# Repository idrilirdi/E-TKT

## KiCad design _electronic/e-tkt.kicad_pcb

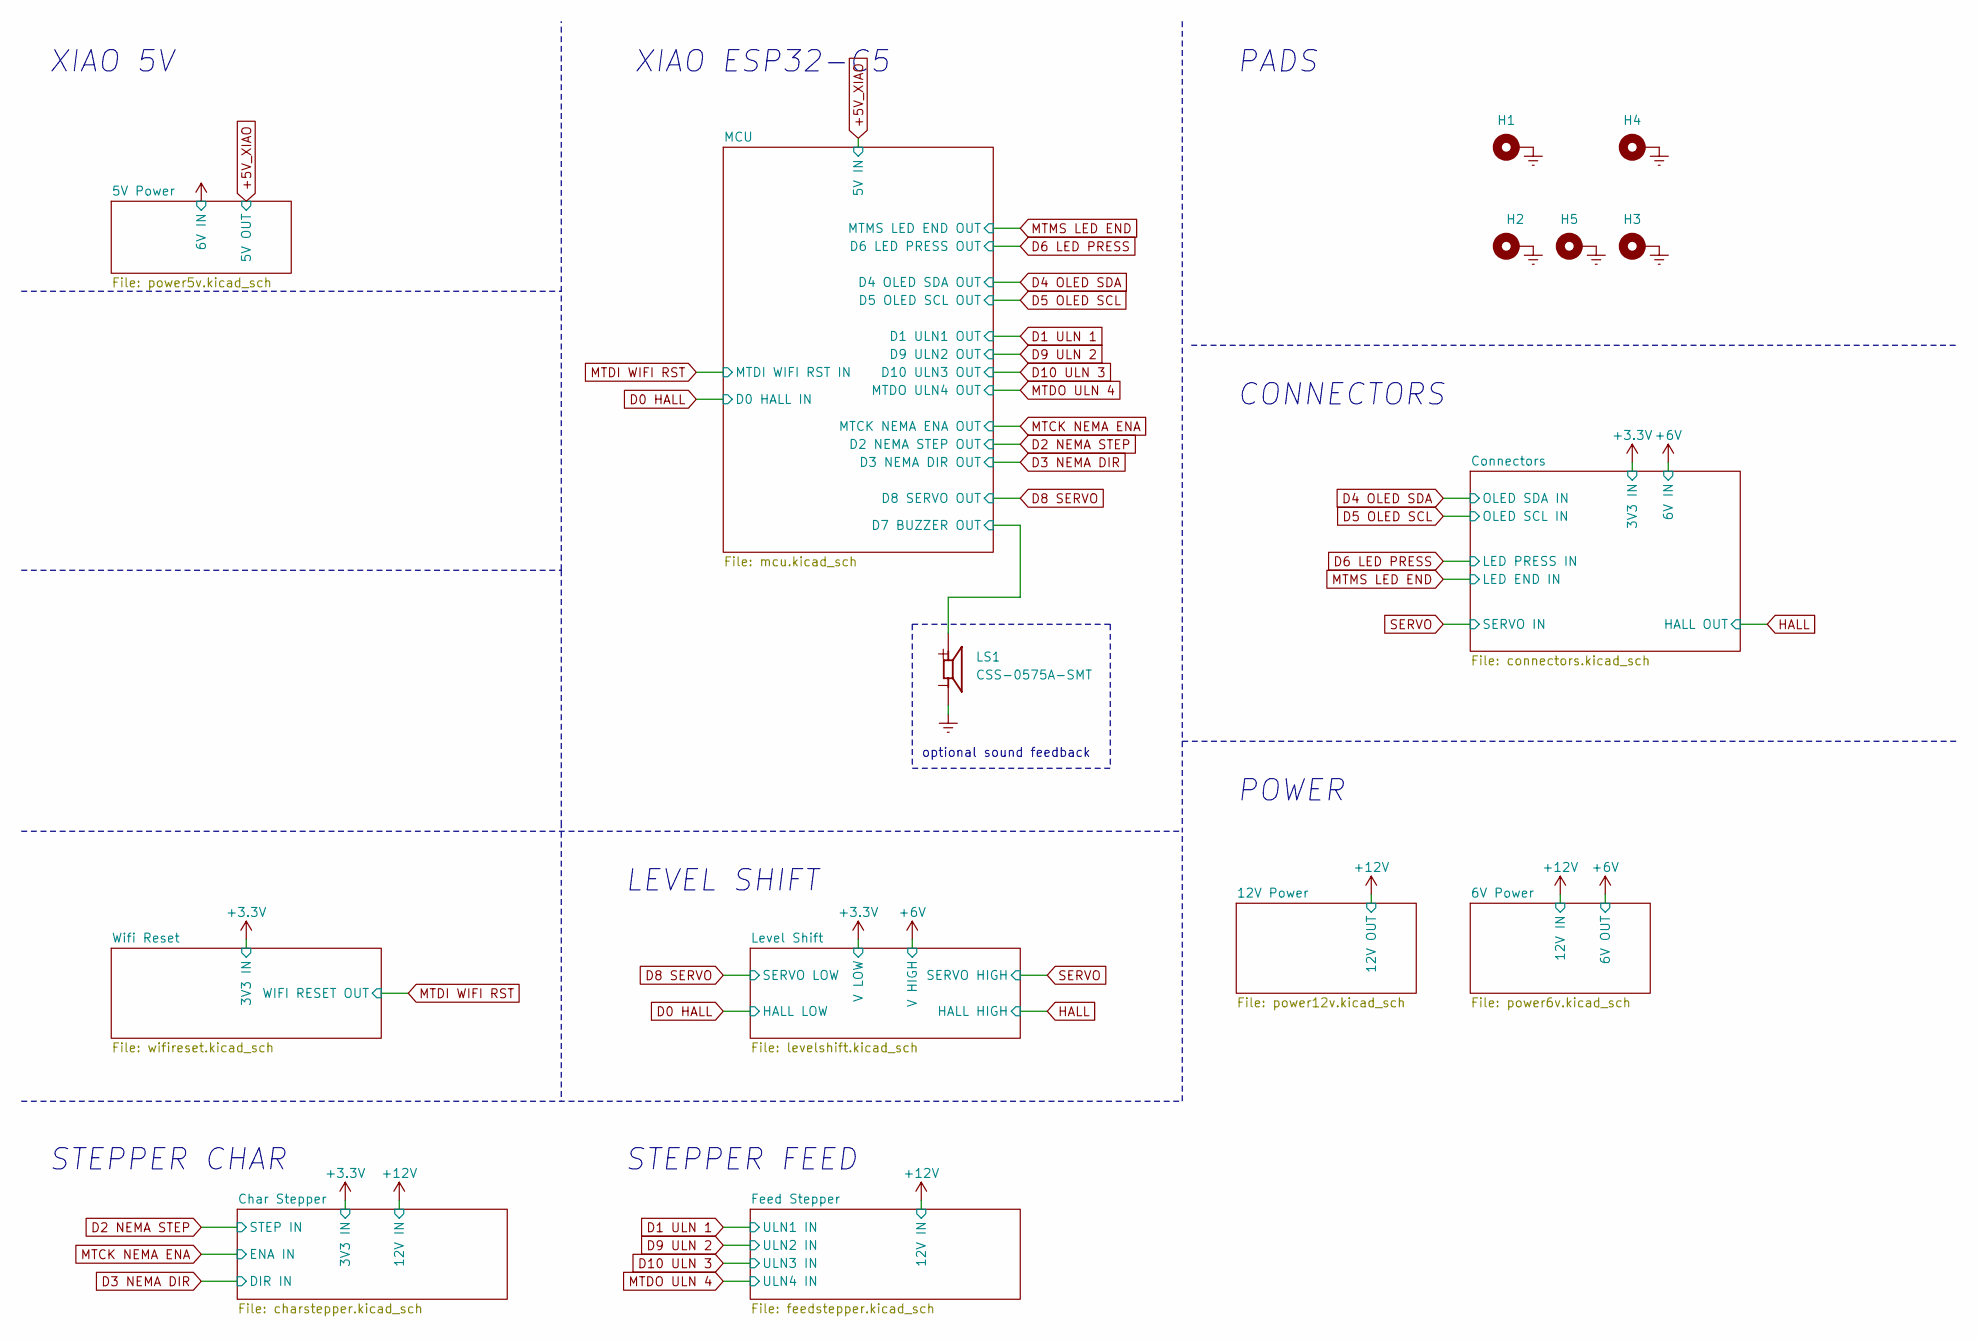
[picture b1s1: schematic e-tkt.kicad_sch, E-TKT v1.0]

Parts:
H1, H2, H3, H4, H5: M3; MountingHole_3.2mm_M3_Pad_Via; Mouser OK
LS1: CSS-0575A-SMT; CUI_CSS-0575A-SMT; Mouser OK

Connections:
/MCU/D7 BUZZER OUT: LS1.1; also elsewhere on the board
GNDREF: H1.1, H2.1, H3.1, H4.1, H5.1, LS1.2; also elsewhere on the board

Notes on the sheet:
PADS
POWER
optional sound feedback
CONNECTORS
STEPPER CHAR
XIAO ESP32-C5
LEVEL SHIFT
STEPPER FEED
XIAO 5V

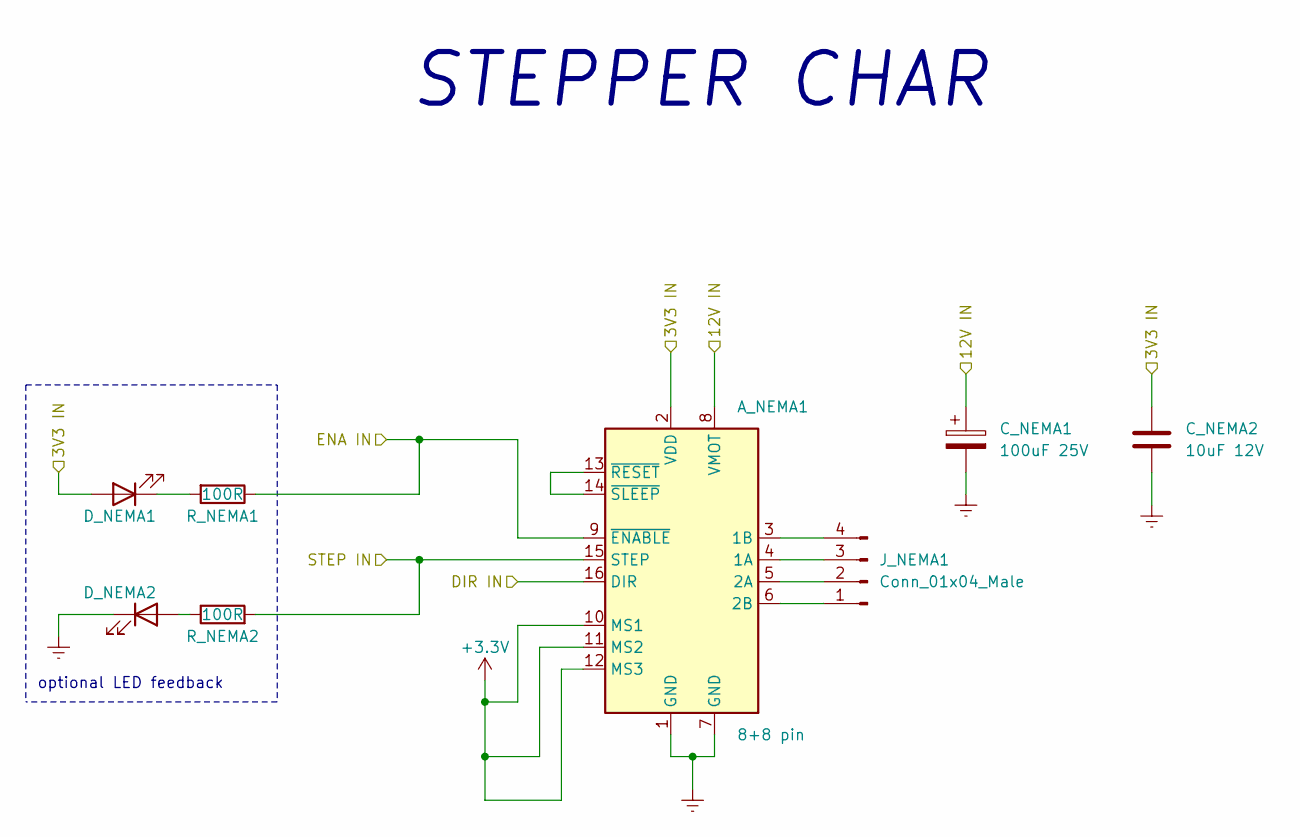
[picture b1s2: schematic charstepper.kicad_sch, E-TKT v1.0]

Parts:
A_NEMA1: 8+8 pin; Pololu_Breakout-16_15.2x20.3mm; Mouser OK
C_NEMA1: 100uF 25V; CP_Elec_6.3x7.7; Mouser OK
C_NEMA2: 10uF 12V; C_0603_1608Metric_Pad1.08x0.95mm_HandSolder; Mouser OK
D_NEMA1, D_NEMA2: LED white; LED_0603_1608Metric_Pad1.05x0.95mm_HandSolder; Mouser OK
J_NEMA1: Conn_01x04_Male; PinHeader_1x04_P2.54mm_Horizontal; Mouser OK
R_NEMA1, R_NEMA2: 100R; R_0603_1608Metric_Pad0.98x0.95mm_HandSolder; Mouser OK

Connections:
+3.3V: A_NEMA1.2 (VDD), A_NEMA1.10 (MS1), A_NEMA1.11 (MS2), A_NEMA1.12 (MS3), C_NEMA2.2, D_NEMA1.2 (A); also elsewhere on the board
+12V: A_NEMA1.8 (VMOT), C_NEMA1.1; also elsewhere on the board
D2 NEMA STEP: A_NEMA1.15 (STEP), R_NEMA2.2; also elsewhere on the board
D3 NEMA DIR: A_NEMA1.16 (DIR); also elsewhere on the board
GNDREF: A_NEMA1.1 (GND), A_NEMA1.7 (GND), C_NEMA1.2, C_NEMA2.1, D_NEMA2.1 (K); also elsewhere on the board
MTCK NEMA ENA: A_NEMA1.9 (~ENABLE), R_NEMA1.1; also elsewhere on the board
unnamed: A_NEMA1.4 (1A), J_NEMA1.3
unnamed: A_NEMA1.3 (1B), J_NEMA1.4
unnamed: A_NEMA1.5 (2A), J_NEMA1.2
unnamed: A_NEMA1.6 (2B), J_NEMA1.1
unnamed: A_NEMA1.13 (~RESET), A_NEMA1.14 (~SLEEP)
unnamed: D_NEMA1.1 (K), R_NEMA1.2
unnamed: D_NEMA2.2 (A), R_NEMA2.1

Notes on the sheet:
optional LED feedback
STEPPER CHAR

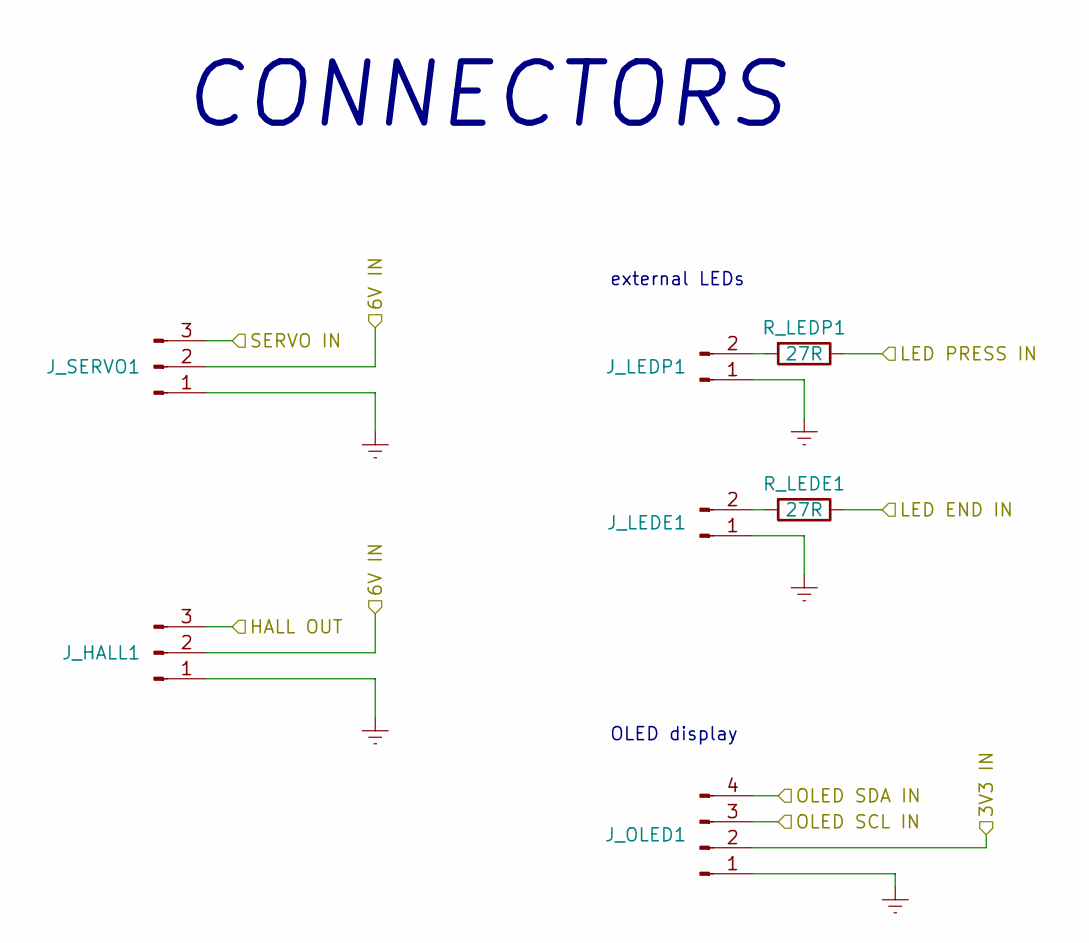
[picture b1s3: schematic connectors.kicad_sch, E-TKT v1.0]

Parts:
J_HALL1: Conn_01x03_Female; PinHeader_1x03_P2.54mm_Vertical; Mouser OK
J_LEDE1: Conn_01x02_Male; PinHeader_1x02_P2.54mm_Vertical; Mouser OK
J_LEDP1: Conn_01x02_Male; PinHeader_1x02_P2.54mm_Vertical; Mouser OK
J_OLED1: Conn_01x04_Male; PinHeader_1x04_P2.54mm_Vertical; Mouser OK
J_SERVO1: Conn_01x03_Male; PinHeader_1x03_P2.54mm_Vertical; Mouser OK
R_LEDE1: 27R; R_0603_1608Metric_Pad0.98x0.95mm_HandSolder; Mouser OK
R_LEDP1: 27R; R_0603_1608Metric_Pad0.98x0.95mm_HandSolder; Mouser OK

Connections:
+3.3V: J_OLED1.2; also elsewhere on the board
+6V: J_HALL1.2, J_SERVO1.2; also elsewhere on the board
D4 OLED SDA: J_OLED1.4; also elsewhere on the board
D5 OLED SCL: J_OLED1.3; also elsewhere on the board
D6 LED PRESS: R_LEDP1.1; also elsewhere on the board
GNDREF: J_HALL1.1, J_LEDE1.1, J_LEDP1.1, J_OLED1.1, J_SERVO1.1; also elsewhere on the board
HALL: J_HALL1.3; also elsewhere on the board
MTMS LED END: R_LEDE1.1; also elsewhere on the board
unnamed: J_LEDE1.2, R_LEDE1.2
unnamed: J_LEDP1.2, R_LEDP1.2
SERVO: J_SERVO1.3; also elsewhere on the board

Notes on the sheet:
OLED display
CONNECTORS
external LEDs

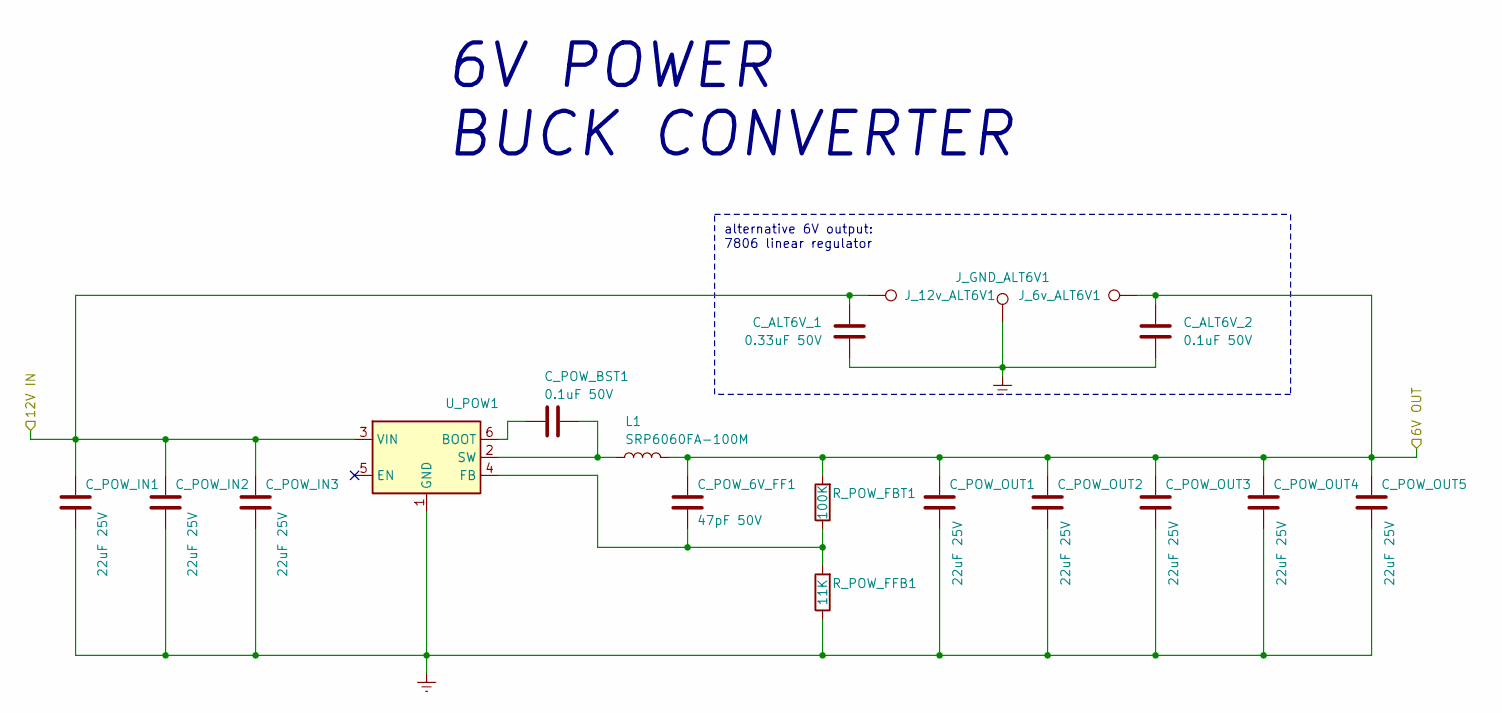
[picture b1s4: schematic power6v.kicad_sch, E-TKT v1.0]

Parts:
C_ALT6V_1: 0.33uF 50V; C_0603_1608Metric_Pad1.08x0.95mm_HandSolder; Mouser OK
C_ALT6V_2: 0.1uF 50V; C_0603_1608Metric_Pad1.08x0.95mm_HandSolder; Mouser OK
C_POW_6V_FF1: 47pF 50V; C_0603_1608Metric_Pad1.08x0.95mm_HandSolder; Mouser OK
C_POW_BST1: 0.1uF 50V; C_0603_1608Metric_Pad1.08x0.95mm_HandSolder; Mouser OK
C_POW_IN1, C_POW_IN2, C_POW_IN3: 22uF 25V; C_1210_3225Metric_Pad1.33x2.70mm_HandSolder; Mouser OK
C_POW_OUT1, C_POW_OUT2, C_POW_OUT3, C_POW_OUT4, C_POW_OUT5: 22uF 25V; C_1210_3225Metric_Pad1.33x2.70mm_HandSolder; Mouser OK
J_6v_ALT6V1, J_12v_ALT6V1: TestPoint; TestPoint_Pad_D1.5mm; Mouser OK
J_GND_ALT6V1: TestPoint; TestPoint_Pad_D1.5mm; Mouser OK
L1: SRP6060FA-100M; SRP6060FA-4R7M; Mouser OK
R_POW_FBT1: 100K; R_0603_1608Metric_Pad0.98x0.95mm_HandSolder; Mouser OK
R_POW_FFB1: 11K; R_0603_1608Metric_Pad0.98x0.95mm_HandSolder; Mouser OK
U_POW1: SOT-23-6_Handsoldering; Mouser N

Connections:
+6V: C_ALT6V_2.1, C_POW_6V_FF1.1, C_POW_OUT1.1, C_POW_OUT2.1, C_POW_OUT3.1, C_POW_OUT4.1, C_POW_OUT5.1, J_6v_ALT6V1.1, L1.2, R_POW_FBT1.2; also elsewhere on the board
+12V: C_ALT6V_1.2, C_POW_IN1.1, C_POW_IN2.1, C_POW_IN3.1, J_12v_ALT6V1.1, U_POW1.3 (VIN); also elsewhere on the board
GNDREF: C_ALT6V_1.1, C_ALT6V_2.2, C_POW_IN1.2, C_POW_IN2.2, C_POW_IN3.2, C_POW_OUT1.2, C_POW_OUT2.2, C_POW_OUT3.2, C_POW_OUT4.2, C_POW_OUT5.2, J_GND_ALT6V1.1, R_POW_FFB1.1, U_POW1.1 (GND); also elsewhere on the board
unnamed: C_POW_BST1.1, U_POW1.6 (BOOT)
unnamed: C_POW_6V_FF1.2, R_POW_FBT1.1, R_POW_FFB1.2, U_POW1.4 (FB)
unnamed: C_POW_BST1.2, L1.1, U_POW1.2 (SW)

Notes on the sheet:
alternative 6V output: 7806 linear regulator
6V POWER BUCK CONVERTER

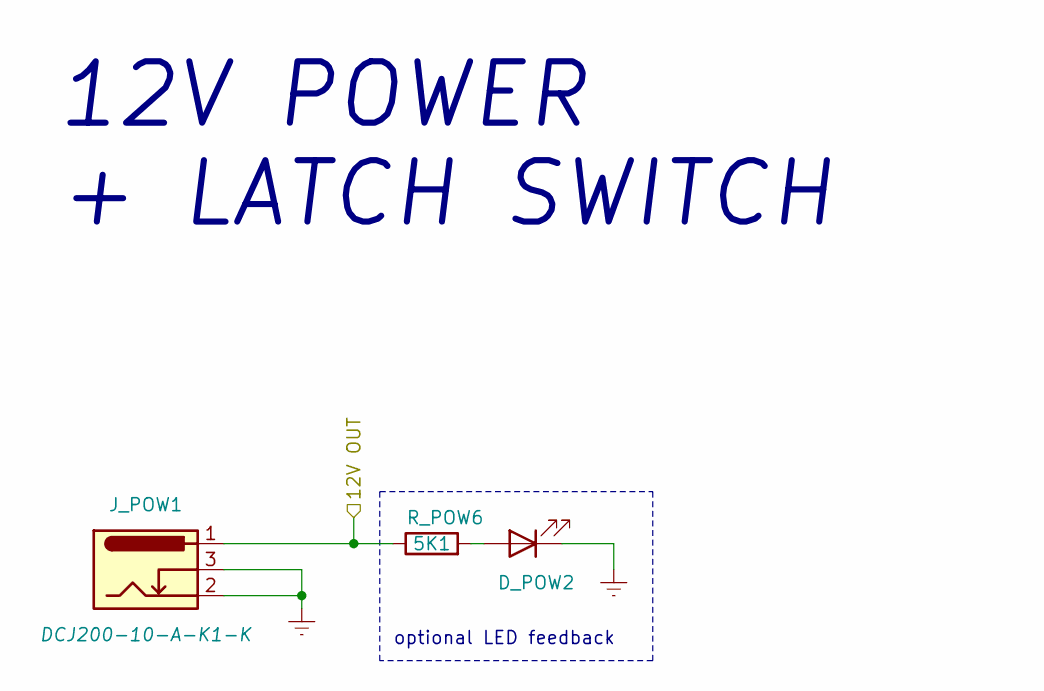
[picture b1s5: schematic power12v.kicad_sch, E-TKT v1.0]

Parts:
D_POW2: LED white; LED_0603_1608Metric_Pad1.05x0.95mm_HandSolder; Mouser OK
J_POW1: Barrel_Jack_Switch; BarrelJack_GCT_DCJ200-10-A_Horizontal; Mouser OK
R_POW6: 5K1; R_0603_1608Metric_Pad0.98x0.95mm_HandSolder; Mouser OK

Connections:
+12V: J_POW1.1, R_POW6.1; also elsewhere on the board
GNDREF: D_POW2.1 (K), J_POW1.2, J_POW1.3; also elsewhere on the board
unnamed: D_POW2.2 (A), R_POW6.2

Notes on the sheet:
optional LED feedback
12V POWER + LATCH SWITCH

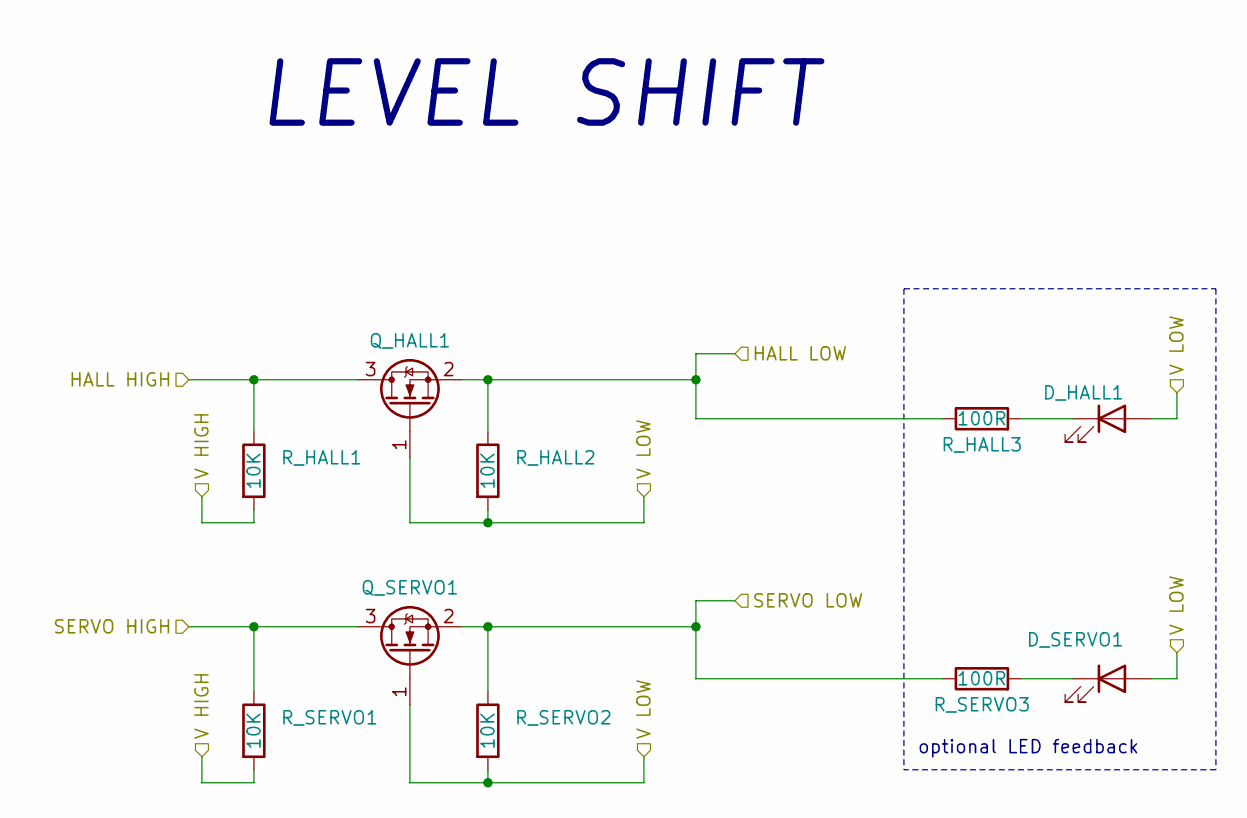
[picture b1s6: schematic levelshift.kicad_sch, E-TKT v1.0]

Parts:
D_HALL1: LED white; LED_0603_1608Metric_Pad1.05x0.95mm_HandSolder; Mouser OK
D_SERVO1: LED white; LED_0603_1608Metric_Pad1.05x0.95mm_HandSolder; Mouser OK
Q_HALL1: BSS138LT3G; SOT-23_Handsoldering; Mouser OK
Q_SERVO1: BSS138LT3G; SOT-23_Handsoldering; Mouser OK
R_HALL1, R_HALL2: 10K; R_0603_1608Metric_Pad0.98x0.95mm_HandSolder; Mouser OK
R_HALL3: 100R; R_0603_1608Metric_Pad0.98x0.95mm_HandSolder; Mouser OK
R_SERVO1, R_SERVO2: 10K; R_0603_1608Metric_Pad0.98x0.95mm_HandSolder; Mouser OK
R_SERVO3: 100R; R_0603_1608Metric_Pad0.98x0.95mm_HandSolder; Mouser OK

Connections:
+3.3V: D_HALL1.2 (A), D_SERVO1.2 (A), Q_HALL1.1 (G), Q_SERVO1.1 (G), R_HALL2.2, R_SERVO2.2; also elsewhere on the board
+6V: R_HALL1.2, R_SERVO1.2; also elsewhere on the board
D0 HALL: Q_HALL1.2 (S), R_HALL2.1, R_HALL3.1; also elsewhere on the board
D8 SERVO: Q_SERVO1.2 (S), R_SERVO2.1, R_SERVO3.1; also elsewhere on the board
HALL: Q_HALL1.3 (D), R_HALL1.1; also elsewhere on the board
unnamed: D_HALL1.1 (K), R_HALL3.2
unnamed: D_SERVO1.1 (K), R_SERVO3.2
SERVO: Q_SERVO1.3 (D), R_SERVO1.1; also elsewhere on the board

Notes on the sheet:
optional LED feedback
LEVEL SHIFT

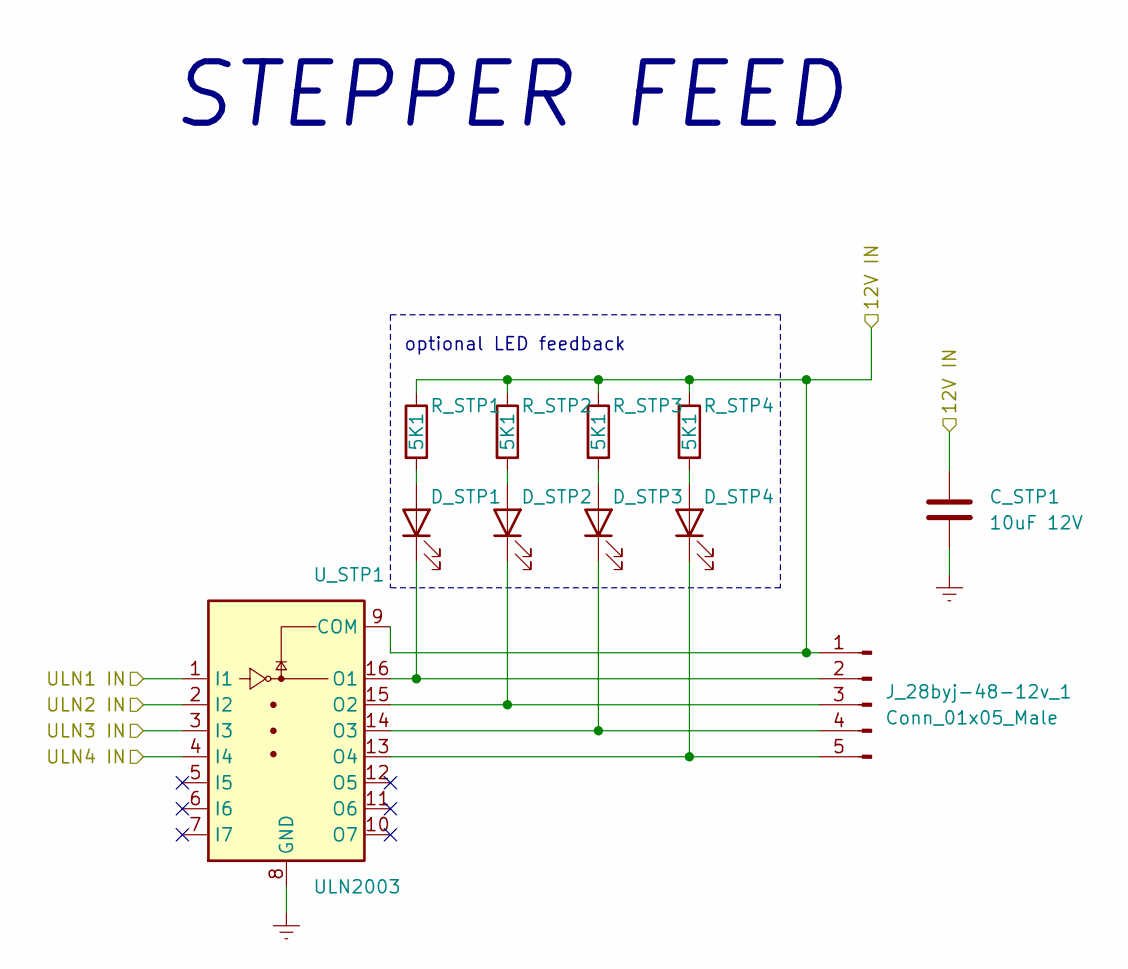
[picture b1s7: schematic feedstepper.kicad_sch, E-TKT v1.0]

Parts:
C_STP1: 10uF 12V; C_0603_1608Metric_Pad1.08x0.95mm_HandSolder; Mouser OK
D_STP1, D_STP2, D_STP3, D_STP4: LED white; LED_0603_1608Metric_Pad1.05x0.95mm_HandSolder; Mouser OK
J_28byj-48-12v_1: Conn_01x05_Male; PinHeader_1x05_P2.54mm_Vertical; Mouser OK
R_STP1, R_STP2, R_STP3, R_STP4: 5K1; R_0603_1608Metric_Pad0.98x0.95mm_HandSolder; Mouser OK
U_STP1: ULN2003; SOIC-16_3.9x9.9mm_P1.27mm; Mouser OK

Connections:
+12V: C_STP1.2, J_28byj-48-12v_1.1, R_STP1.1, R_STP2.1, R_STP3.1, R_STP4.1, U_STP1.9 (COM); also elsewhere on the board
D1 ULN 1: U_STP1.1 (I1); also elsewhere on the board
D9 ULN 2: U_STP1.2 (I2); also elsewhere on the board
D10 ULN 3: U_STP1.3 (I3); also elsewhere on the board
GNDREF: C_STP1.1, U_STP1.8 (GND); also elsewhere on the board
MTDO ULN 4: U_STP1.4 (I4); also elsewhere on the board
unnamed: D_STP1.2 (A), R_STP1.2
unnamed: D_STP1.1 (K), J_28byj-48-12v_1.2, U_STP1.16 (O1)
unnamed: D_STP2.2 (A), R_STP2.2
unnamed: D_STP2.1 (K), J_28byj-48-12v_1.3, U_STP1.15 (O2)
unnamed: D_STP3.2 (A), R_STP3.2
unnamed: D_STP3.1 (K), J_28byj-48-12v_1.4, U_STP1.14 (O3)
unnamed: D_STP4.2 (A), R_STP4.2
unnamed: D_STP4.1 (K), J_28byj-48-12v_1.5, U_STP1.13 (O4)

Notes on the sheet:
optional LED feedback
STEPPER FEED

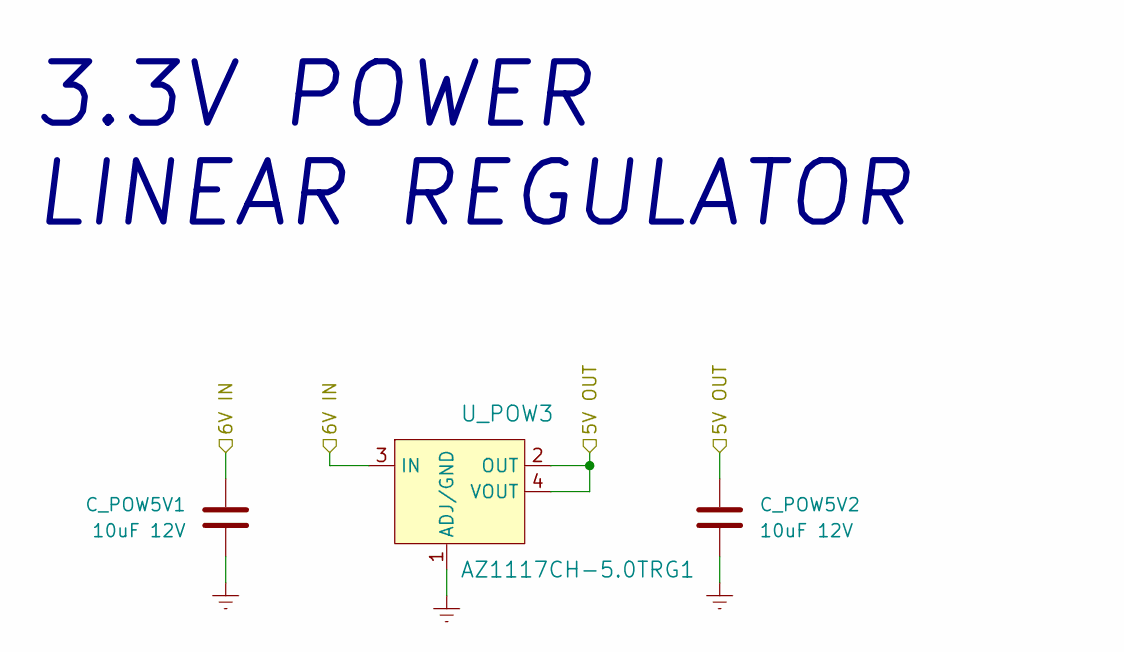
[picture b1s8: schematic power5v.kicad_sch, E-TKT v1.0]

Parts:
C_POW5V1, C_POW5V2: 10uF 12V; C_0603_1608Metric_Pad1.08x0.95mm_HandSolder; Mouser OK
U_POW3: AZ1117CH-5.0TRG1; SOT-223; Mouser OK

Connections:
+5V_XIAO: C_POW5V2.1, U_POW3.2 (OUT), U_POW3.4 (VOUT); also elsewhere on the board
+6V: C_POW5V1.1, U_POW3.3 (IN); also elsewhere on the board
GNDREF: C_POW5V1.2, C_POW5V2.2, U_POW3.1 (ADJ/GND); also elsewhere on the board

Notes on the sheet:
3.3V POWER LINEAR REGULATOR

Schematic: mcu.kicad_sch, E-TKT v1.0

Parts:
D_VBUS1: SS14; D_SMA
SW_DFU1: B3FS-1000
U_MCU1: XIAO-ESP32-C5; XIAO-ESP32-C5-SMD

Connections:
+3.3V: U_MCU1.12 (3V3_OUT); also elsewhere on the board
+5V_XIAO: D_VBUS1.2 (A); also elsewhere on the board
/MCU/D7 BUZZER OUT: U_MCU1.8 (D7); also elsewhere on the board
D0 HALL: U_MCU1.1 (D0); also elsewhere on the board
D1 ULN 1: U_MCU1.2 (D1); also elsewhere on the board
D2 NEMA STEP: U_MCU1.3 (D2); also elsewhere on the board
D3 NEMA DIR: U_MCU1.4 (D3); also elsewhere on the board
D4 OLED SDA: U_MCU1.5 (D4); also elsewhere on the board
D5 OLED SCL: U_MCU1.6 (D5); also elsewhere on the board
D6 LED PRESS: U_MCU1.7 (D6); also elsewhere on the board
D8 SERVO: U_MCU1.9 (D8); also elsewhere on the board
D9 ULN 2: U_MCU1.10 (D9); also elsewhere on the board
D10 ULN 3: U_MCU1.11 (D10); also elsewhere on the board
GNDREF: SW_DFU1.2, SW_DFU1.4, U_MCU1.13 (GND), U_MCU1.18 (GND), U_MCU1.24 (GND), U_MCU1.25 (PAD); also elsewhere on the board
MTCK NEMA ENA: U_MCU1.20 (MTCK); also elsewhere on the board
MTDI WIFI RST: U_MCU1.15 (MTDI); also elsewhere on the board
MTDO ULN 4: U_MCU1.16 (MTDO); also elsewhere on the board
MTMS LED END: U_MCU1.19 (MTMS); also elsewhere on the board
unnamed: D_VBUS1.1 (K), U_MCU1.14 (VBUS)
unnamed: SW_DFU1.1, SW_DFU1.3, U_MCU1.21 (BOOT)

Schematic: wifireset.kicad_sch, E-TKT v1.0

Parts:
C_WIFI1: 0.1uF 50V; C_0603_1608Metric_Pad1.08x0.95mm_HandSolder; Mouser OK
R_WIFI1: 10K; R_0603_1608Metric_Pad0.98x0.95mm_HandSolder; Mouser OK
SW_WIFI1: B3FS-1000; Mouser OK

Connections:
+3.3V: R_WIFI1.2; also elsewhere on the board
GNDREF: C_WIFI1.1, SW_WIFI1.1, SW_WIFI1.2; also elsewhere on the board
MTDI WIFI RST: C_WIFI1.2, R_WIFI1.1, SW_WIFI1.3, SW_WIFI1.4; also elsewhere on the board

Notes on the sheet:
WIFI RESET

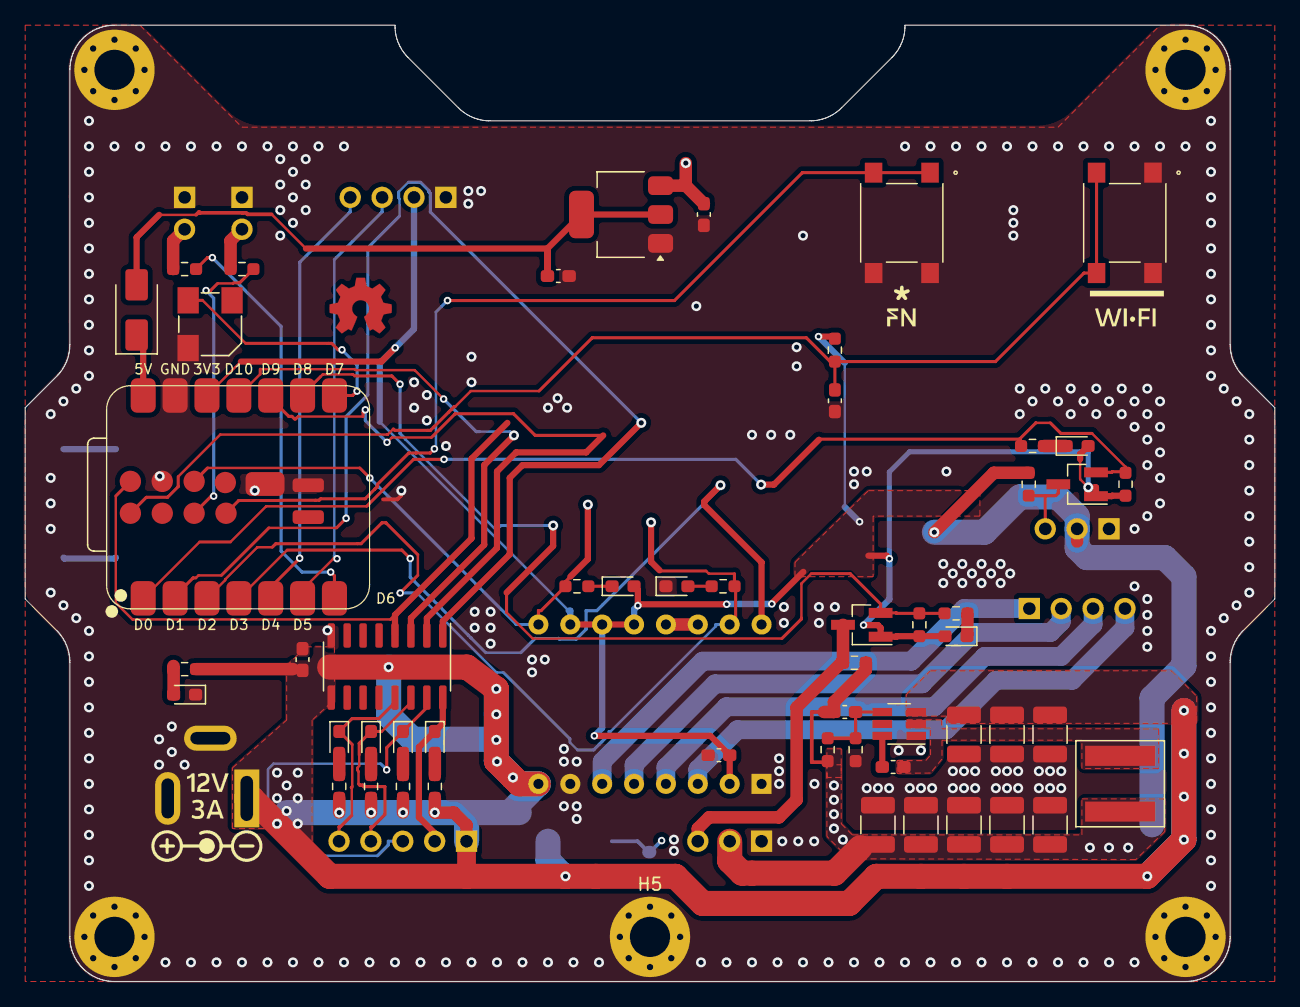
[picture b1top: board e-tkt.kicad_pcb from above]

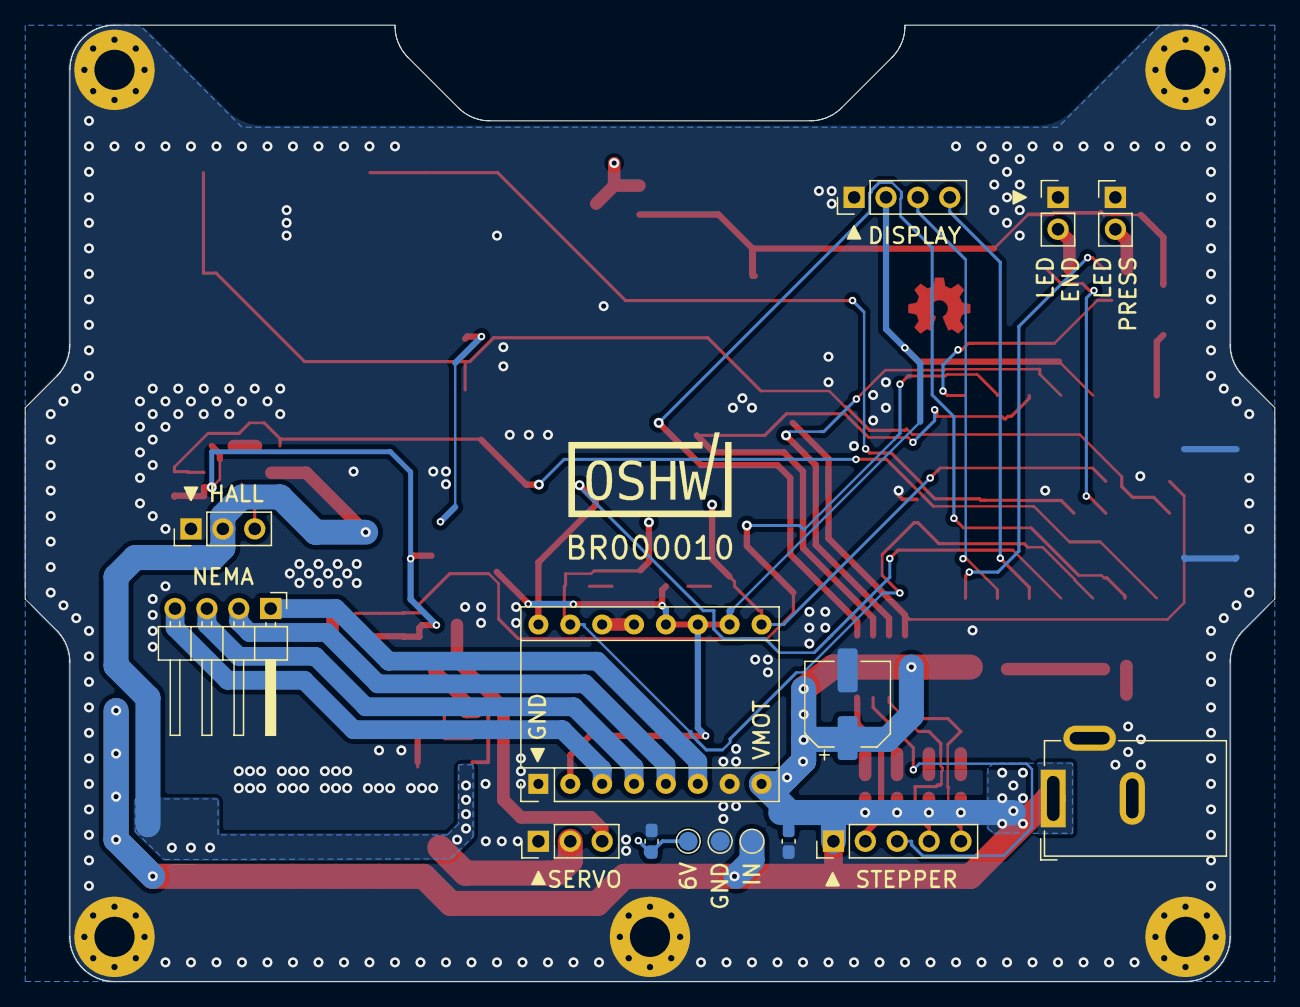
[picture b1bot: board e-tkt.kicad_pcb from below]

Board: 4 copper layers, 99.6 x 76.2 mm, 73 parts (15 on the bottom side), 47 nets.

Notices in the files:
parts and their libraries:
Copyright 2021 Accelerated Designs. All rights reserved.
